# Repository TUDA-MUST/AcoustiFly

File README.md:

# AcoustiFly, a single transducer Acoustic Levitator

Unlock the Power of Sound: Explore Acoustic Levitation with Ease and Precision.
This project focuses on the development of an acoustic levitator, a fascinating technology capable of suspending small objects in mid-air using ultrasonic waves.
It is:
* **Low Cost:** Affordable and accessible to everyone -> approximately between 15-25 USD per unit
* **Easy to Build:** Simple setup with readily available components
* **Open Source:** Free to use, modify, and distribute
* **Mobile:** Battery powered operation possible
* **Adjustable:** Distance between transducer and reflector can be adjusted, thus stability can be tuned

This repository provides all the necessary resources, including code, schematics, and documentation, to build and experiment with your very own acoustic levitation system.

***

## Table of Contents

- [Introduction](#introduction)
- [Installation](#installation)
- [Assemby](#assembly)
- [Usage](#usage)
- [Contributing](#contributing)
- [License](#license)
- [Frequently Asked Questions \(FAQ\)](#frequently-asked-questions-faq)

## Introduction

Our repository is dedicated to showcasing a method of acoustic levitation using a single transducer and a reflector. Acoustic levitation, also known as acoustic trapping, is a fascinating technique that allows objects to float in mid-air using sound waves.

In our approach, we utilize a single transducer, which emits high-frequency sound waves, and a carefully designed reflector. 
The transducer generates an acoustic field that interacts with the reflector to create standing waves within a confined region. 
These standing waves produce regions of high and low pressure, forming what is known as an "acoustic pressure node".

When an object is placed at a specific position within the acoustic pressure node, the forces exerted by the surrounding sound waves counteract the gravitational force, resulting in levitation. By precisely adjusting the distance of the transducer and the reflector, we can control the levitation height and stability of objects.

This unique approach offers several advantages. 
Firstly, it simplifies the setup by using only a single transducer and a reflector, reducing complexity and cost. 
Secondly, it enables precise control over the levitation process, allowing for manipulation and positioning of objects with great accuracy. 
Lastly, it opens up possibilities for various applications, including material handling, microfluidics, and scientific experiments.

In our repository, we provide detailed documentation, source code, and demonstrations to help you understand and implement this acoustic levitation technique.
 Whether you are a researcher, teacher, hobbyist, or enthusiast, we invite you to explore our repository, contribute to its development, and unlock the potential of acoustic levitation with a single transducer and a reflector.

**Join us on this exciting journey of harnessing the power of sound waves to defy gravity. Visit [our homepage](https://www.etit.tu-darmstadt.de/must/home_must/index.en.jsp) to delve into our research and learn more about our team.**

## Assembly
To assemble the Acoustifly you will need the following components:

* **3D-printed:**

  Base, Battery-Cover, Transducer-Holder, Vertical profile
* **Electrical Components:**

  UT-1640K-TT-2-R Transducer, Transducer PCB, Acoustifly PCB, EXP-T11-020 3.7V 720mAh Lithium Polymer Battery with JST-PH connector,
* **Others:**

  Ruthex M3s threaded inserts, M3 screws

### Instructions:
1. To install the threaded inserts you need to heat them up to 230°C. Best is to use a soldering tip to melt them into the 3D-printed parts.

2. Mount the Transducer PCB with the Tranducer on the Transducer holder:

3. Attach it to the vertical profile:

4. Screw the complete Tranducer Holder to the Base:

5. Put the Transducer cord through the two holes on the Base and solder them to the PCB:

6. Install the Acoustifly PCB into the Base and connect the JST-Connector. After that you can also connect the Battery-cover:

7. Close the cover and enjoy your Acoustifly!:

## Installation

### PlatformIO
Here's a [Quickstart Guide](https://docs.platformio.org/en/latest/integration/ide/vscode.html#quick-start) on how to use Platform IO with Visual Studio Code.
### Arduino IDE
To enable working with the underlying microcontroller (ESP32-S3-MINI-1-N4R2) you are required to install the relevant board package. To do this, open _Tools > Board > Boards Manager_ and install the _'esp32'_ package by Espressif Systems.\
The Board should be set to `Adafruit Feather ESP32-S3 2MB PSRAM` as this comes closest to the used microcontroller. The relevant options under Tools should be set according to the following image. Make sure to enable `USB CDC on Boot`, which permits USB communication.

### Uploading Code
Since this board does not use a separate usb-to-serial chip, the microcontroller needs to be put into the bootloading state manually. To accomplish this, simply hold down down the <kbd> BOOT </kbd> button on the PCB and then quickly press the <kbd> Reset </kbd> button once. After releasing the <kbd> BOOT </kbd> button, you are now able to upload your code.\
_! The COM Port is likely to change after entering Boot-mode and may need to be set again in your Software !_

## Usage

### Pinout
| Pin | Name | Description |
|-----|------|-------------|
|1|LED_YELLOWGREEN|emits yellow-green light (current sink!)|
|2|LED_RED|emits red light (current sink!)|
|4|HBRIDGE_ENABLE      |HIGH enables the h_bridge/output for both transducers|
|5|HBRIDGE_A_NORMAL|PWM Input for Transducers A|
|6|HBRIDGE_A_INVERTED|inverted PWM Input for Transducers A|
|7|HBRIDGE_B_NORMAL|PWM Input for Transducers B|
|8|HBRIDGE_B_INVERTED|inverted PWM Input for Transducers B|
|9|HBRIDGE_CURRENTSENSE|read analog voltage to measure transducer current consumption|
|10|BAT_STATE      |used to read battery voltage|
|40|MISO      |SCPI|
|41|SCK      |SCPI|
|41|MOSI      |SCPI|

The **LED**s are setup in a current sink configuration, meaning a LOW signal will emit light while a HIGH signal will shut them off. Consider the command `GPIO.func_out_sel_cfg[PIN].inv_sel = 1` to reverse this. \
The **HBRIDGE_*** inputs require either the typical PWM signal or the inverted one. The easiest way to achieve this is to set both to the same [LEDC Channel](https://docs.espressif.com/projects/esp-idf/en/stable/esp32/api-reference/peripherals/ledc.html) and invert one output with the already mentioned command. \
**CURRENTSENSE** can be used to measure the current consumption of the h-bridge, so both transducers simultaneously. 
Current is measured via a 500mΩ high side shunt. 
The voltage across which is amplified by a factor of 100 and then averaged with a low pass filter. 
As a result, the average current consumption can be calculated by measuring the voltage on Pin "HBRIDGE_CURRENTSENSE" and dividing it by 50.\
**BAT_STATE** can be used to read the battery voltage. However, it is reduced by a voltage divider. Multiply the measured voltage by 11 to read the correct voltage level. \
_! As a small sidenote, the used microcontroller ESP32 does not have a very accurate, integrated ADC. However, finding the peak voltage is sufficient to determine the resonant frequency. !_

## License

This project is licensed under the GNU GENERAL PUBLIC LICENSE Version 3, 29 June 2007. Please see the [LICENSE](LICENSE) file for more details.

## Reference

If you would like to reference our project, feel free to support us by citing our research paper:\
[AcoustiFly: An Open-Source, Low-Cost Acoustic Levitator for Hands-On STEM Education](https://doi.org/10.1109/EDUCON62633.2025.11016546)
```
@inproceedings{Suppelt2025,
  title = {AcoustiFly: An Open-Source,  Low-Cost Acoustic Levitator for Hands-On STEM Education},
  url = {http://dx.doi.org/10.1109/educon62633.2025.11016546},
  DOI = {10.1109/educon62633.2025.11016546},
  booktitle = {2025 IEEE Global Engineering Education Conference (EDUCON)},
  publisher = {IEEE},
  author = {Suppelt,  Mark and Suppelt,  Sven and D\"{o}rsam,  Jan Helge and Altmann,  Alexander A. and Kupnik,  Mario},
  year = {2025},
  month = apr,
  pages = {1–5}
}
```
(or click [here](https://doi.org/10.26083/tuprints-00031137) if you want to read the paper without having to go through a paywall)

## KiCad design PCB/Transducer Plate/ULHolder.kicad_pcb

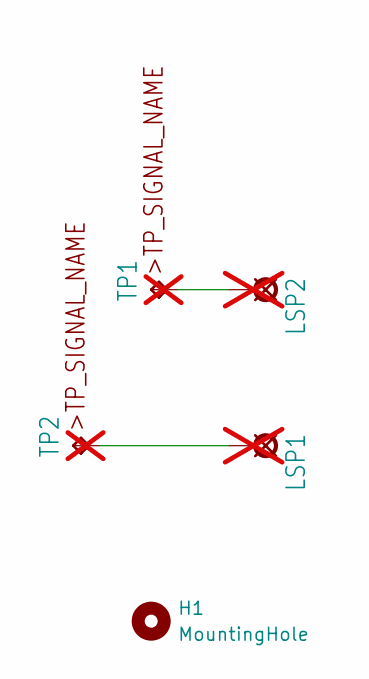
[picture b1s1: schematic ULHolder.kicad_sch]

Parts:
H1: MountingHole; MountingHole_3.2mm_M3
LSP1, LSP2: MCS08; not fitted
TP1, TP2: TPTP20SQ; TP20SQ; not fitted

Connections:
unnamed: LSP1.MP, TP2.TP
unnamed: LSP2.MP, TP1.TP

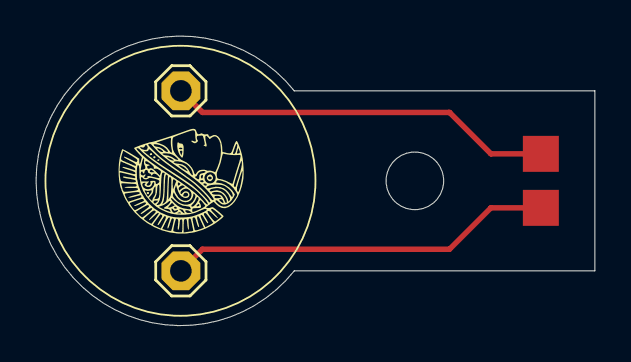
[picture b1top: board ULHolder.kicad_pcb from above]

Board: 2 copper layers, 31.0 x 16.1 mm, 5 parts (0 on the bottom side), 2 nets.

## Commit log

2024-10-30 Initial
2024-12-09 Added Assembly Instructions
2024-12-10 added mobile application
2025-01-03 edited help message
